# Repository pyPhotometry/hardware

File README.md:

# pyPhotometry Hardware

This repository contains design files for pyPhometry hardware.  For more information see: https://pyphotometry.readthedocs.io/en/latest/user-guide/hardware/

The repository contains the following devices:

## Acquisition board v1.0

The original version of the acquisition board as detailed in the [pyPhotometry manuscript](https://www.nature.com/articles/s41598-019-39724-y), featuring:

-  2 analog inputs (0-3.3V) for photoreceiver signals.
- 2 Digital inputs for registering behavioural events or sync pulses.
- 2 LED driver outputs with 0-100mA adjustable current output.

## Acquisition board v2.0

An updated version of the acquisition board with the following improvements from version 1.0:

- Increased maximum current of 300mA from the two LED driver outputs.
- 2 additional LED control outputs for triggering external LED drivers that require a voltage control signal (0-3.3V) , allowing the board to be used with optical hardware like the Doric Gen3 minicubes which have integrated LED drivers.  The signals output on the two LED control outputs are the same signals used to control the on-board LED drivers, so it is not possible to independently use the LED control outputs and the LED driver outputs at the same time.
- Reduced artefacts on analog input signals caused by saturation (i.e. voltage exceeding 3.3V) on the other analog input.
- Additional Picoblade connector providing access to 3 pyboard pins including I2C serial communication.  

## Acquisition board case

A plastic case compatible both v1.0 and v2.0 acquisition boards.

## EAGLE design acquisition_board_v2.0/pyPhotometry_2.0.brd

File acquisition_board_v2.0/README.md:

# Acquisition board v2.0

An updated version of the acquisition board with the following improvements from version 1.0:

- Increased maximum current of 300mA from the two LED driver outputs.
- 2 additional LED control outputs for triggering external LED drivers that require a voltage control signal (0-3.3V) , allowing the board to be used with optical hardware like the Doric Gen3 minicubes which have integrated LED drivers.  The signals output on the two LED control outputs are the same signals used to control the on-board LED drivers, so it is not possible to independently use the LED control outputs and the LED driver outputs at the same time.
- Reduced artefacts on analog input signals caused by saturation (i.e. voltage exceeding 3.3V) on the other analog input.
- Additional Picoblade connector providing access to 3 pyboard pins including I2C serial communication.

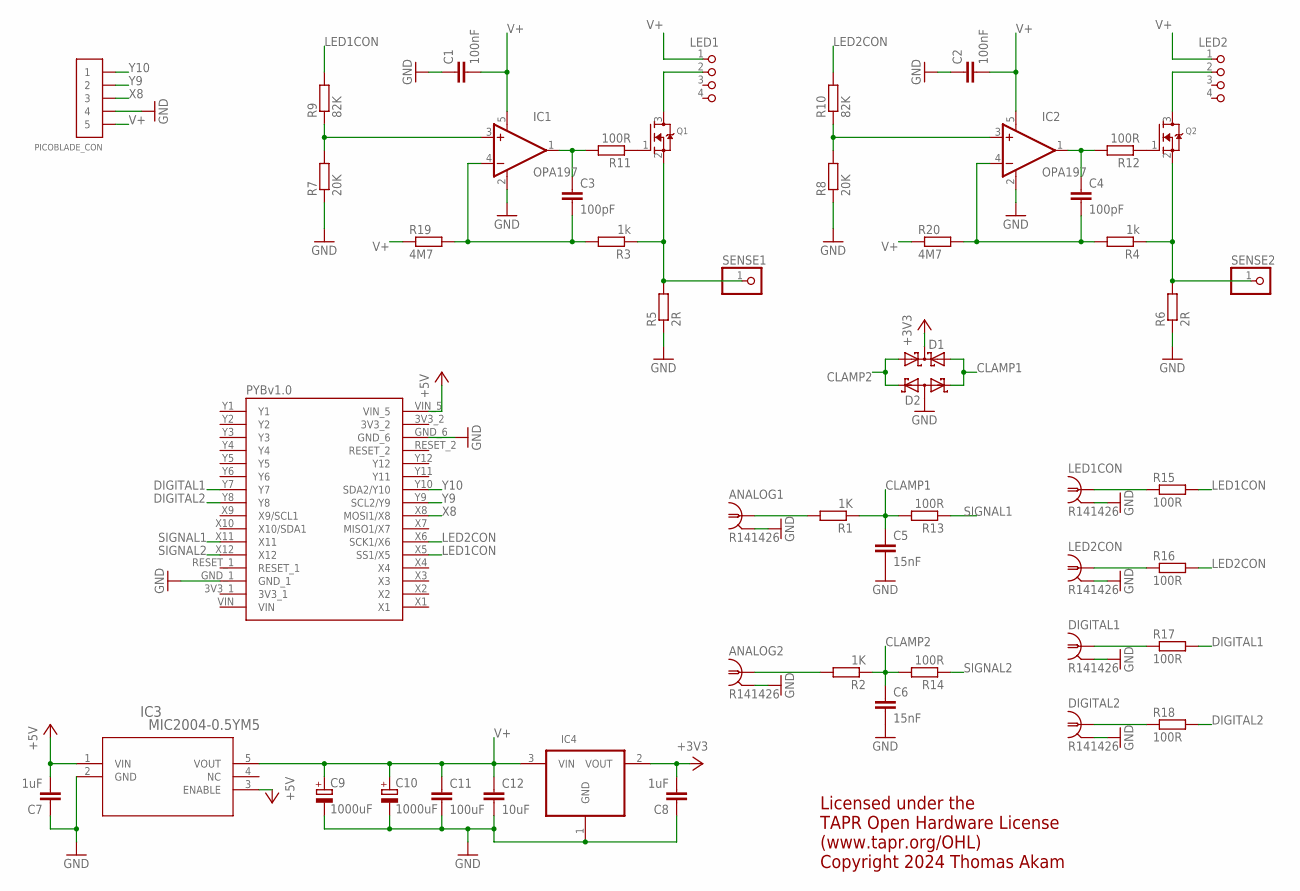
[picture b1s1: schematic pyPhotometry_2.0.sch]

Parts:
ANALOG1, ANALOG2: R141426
C1: 100nF; C0603K
C2: 100nF; C0603
C3, C4: 100pF; C0603K
C5, C6: 15nF; C0603K
C7, C8: 1uF; C0603
C9, C10: 1000uF; 153CLV-0807
C11: 100uF; C1206
C12: 10uF; C1206
D1: BAT54C; SOT23
D2: BAT54A; SOT23
DIGITAL1, DIGITAL2: R141426
IC1, IC2: OPA197; SOT23-5
IC3: MIC2004-0.5YM5; SOT-23-5_M5
IC4: MCP1700T-3302E/TT; SOT95P237X112-3N
LED1, LED2: M8-4
LED1CON, LED2CON: R141426
PICOBLADE_CON: CONN_5-1-53261; PB-53261-05
Q1, Q2: MOSFET-NREFLOW; SOT23
R1, R2: 1K; R0603
R3, R4: 1k; R0603
R5, R6: 2R; R0603
R7, R8: 20K; R0603
R9, R10: 82K; R0603
R11, R12, R13, R14, R15, R16, R17, R18: 100R; R0603
R19, R20: 4M7; R0603
SENSE1, SENSE2: PINHD-1X1; 1X01
U$1: PYBOARD-REDUCED-3

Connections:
+3V3: C8.2, D1.3 (CC), IC4.2 (VOUT)
+5V: C7.2, IC3.1 (VIN), IC3.3 (ENABLE), U$1.VIN_5
A1: ANALOG1.1, R1.2
A2: ANALOG2.1, R2.2
CLAMP1: C5.1, D1.2 (A2), D2.1 (K1), R1.1, R13.2
CLAMP2: C6.1, D1.1 (A1), D2.2 (K2), R2.1, R14.2
DIGITAL1: R17.2, U$1.Y7
DIGITAL2: R18.2, U$1.Y8
GND: ANALOG1.2 (GND), ANALOG1.3 (GND), ANALOG1.4 (GND), ANALOG1.5 (GND), ANALOG2.2 (GND), ANALOG2.3 (GND), ANALOG2.4 (GND), ANALOG2.5 (GND), C1.1, C2.1, C5.2, C6.2, C7.1, C8.1, C9.-, C10.-, C11.2, C12.2, D2.3 (AA), DIGITAL1.2 (GND), DIGITAL1.3 (GND), DIGITAL1.4 (GND), DIGITAL1.5 (GND), DIGITAL2.2 (GND), DIGITAL2.3 (GND), DIGITAL2.4 (GND), DIGITAL2.5 (GND), IC1.2 (V-), IC2.2 (V-), IC3.2 (GND), IC4.1 (GND), LED1CON.2 (GND), LED1CON.3 (GND), LED1CON.4 (GND), LED1CON.5 (GND), LED2CON.2 (GND), LED2CON.3 (GND), LED2CON.4 (GND), LED2CON.5 (GND), PICOBLADE_CON.4, R5.1, R6.1, R7.1, R8.1, U$1.GND_1, U$1.GND_6
LED1CON: R9.2, R15.2, U$1.X5 (SS1/X5)
LED2CON: R10.2, R16.2, U$1.X6 (SCK1/X6)
unnamed: C3.1, IC1.1 (OUT), R11.2
unnamed: C3.2, IC1.4 (-IN), R3.2, R19.2
unnamed: IC1.3 (+IN), R7.2, R9.1
unnamed: Q1.1 (G), R11.1
unnamed: LED1.2, Q1.3 (D)
unnamed: Q1.2 (S), R3.1, R5.2, SENSE1.1
unnamed: C4.1, IC2.1 (OUT), R12.2
unnamed: Q2.2 (S), R4.1, R6.2, SENSE2.1
unnamed: C4.2, IC2.4 (-IN), R4.2, R20.2
unnamed: IC2.3 (+IN), R8.2, R10.1
unnamed: Q2.1 (G), R12.1
unnamed: LED2.2, Q2.3 (D)
unnamed: DIGITAL1.1, R17.1
unnamed: LED1CON.1, R15.1
unnamed: DIGITAL2.1, R18.1
unnamed: LED2CON.1, R16.1
SIGNAL1: R13.1, U$1.X11
SIGNAL2: R14.1, U$1.X12
V+: C1.2, C2.2, C9.+, C10.+, C11.1, C12.1, IC1.5 (V+), IC2.5 (V+), IC3.5 (VOUT), IC4.3 (VIN), LED1.1, LED2.1, PICOBLADE_CON.5, R19.1, R20.1
X8: PICOBLADE_CON.3, U$1.X8 (MOSI1/X8)
Y9: PICOBLADE_CON.2, U$1.Y9 (SCL2/Y9)
Y10: PICOBLADE_CON.1, U$1.Y10 (SDA2/Y10)

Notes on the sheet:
Licensed under the TAPR Open Hardware License (www.tapr.org/OHL) Copyright 2024 Thomas Akam

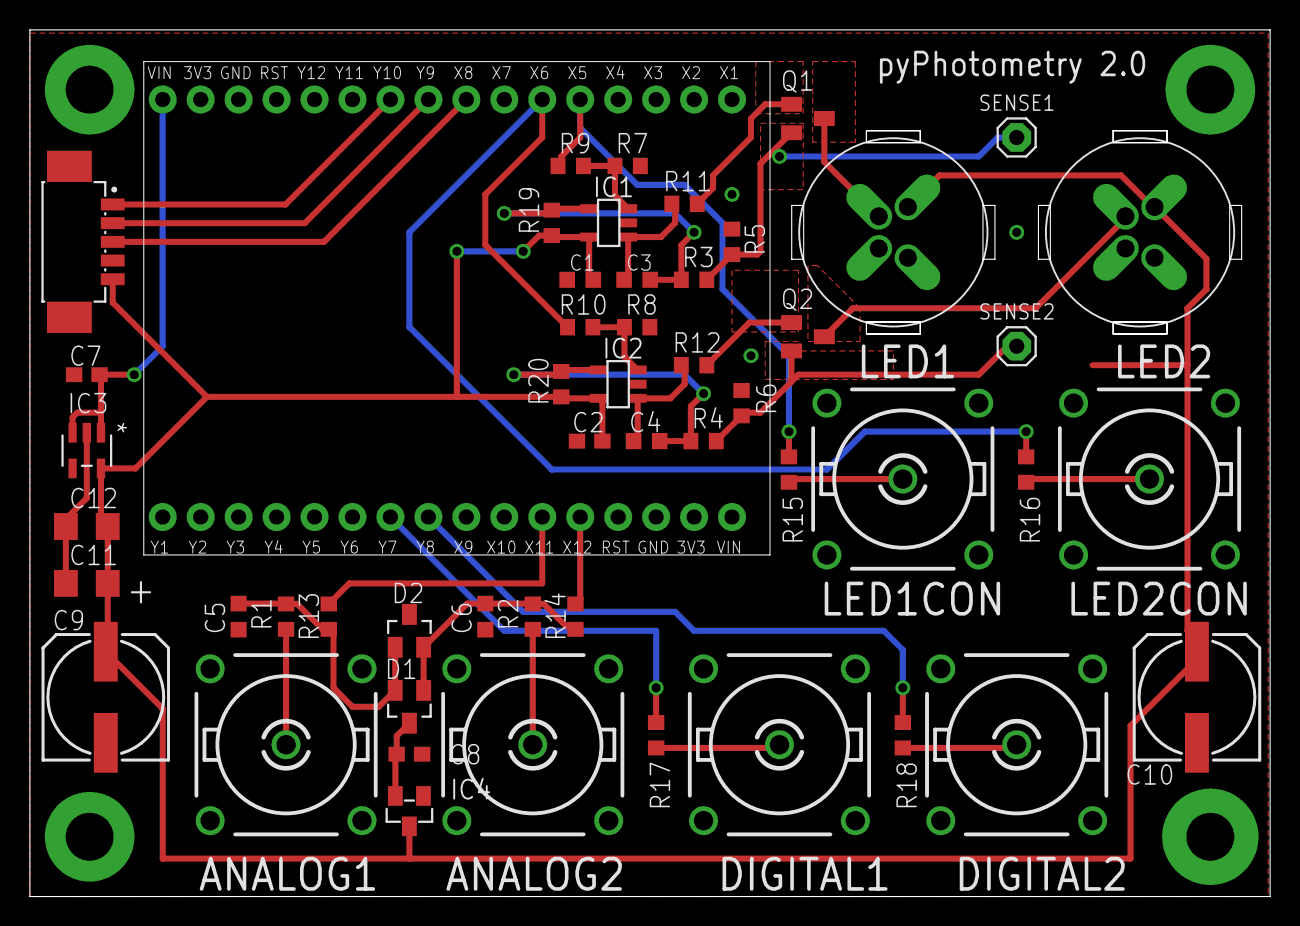
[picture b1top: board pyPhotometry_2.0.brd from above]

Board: 2 copper layers, 83.0 x 58.0 mm, 52 parts (0 on the bottom side), 33 nets.

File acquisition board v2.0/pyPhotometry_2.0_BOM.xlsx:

Part | Value | Device | Package | Description | MF | MPN | OC_FARNELL
SIGNAL1 |  | - | - | BNC connector | TE CONNECTIVITY | 1-1337445-0 | 1205964
SIGNAL2 |  | - | - | BNC connector | TE CONNECTIVITY | 1-1337445-0 | 1205964
DIGITAL1 |  | - | - | BNC connector | TE CONNECTIVITY | 1-1337445-0 | 1205964
DIGITAL2 |  | - | - | BNC connector | TE CONNECTIVITY | 1-1337445-0 | 1205964
LED1CON |  | - | - | BNC connector | TE CONNECTIVITY | 1-1337445-0 | 1205964
LED2CON |  | - | - | BNC connector | TE CONNECTIVITY | 1-1337445-0 | 1205964
LED1 | - | - | - | M8 connector | TE CONNECTIVITY | T4041037041-000 | 2817801
LED2 | - | - | - | M8 connector | TE CONNECTIVITY | T4041037041-000 | 2817801
PICOBLADE_CON | - | - | - | Picoblade connector | Molex | 53261-0571 | 1125360
IC1 | - | OPA197 | SOT23-5 | Op amp | Texas Instruments | OPA197IDBVT | 2545356
IC2 | - | OPA197 | SOT23-5 | Op amp | Texas Instruments | OPA197IDBVT | 2545356
IC3 | - | MIC2004-0.5YM5 | SOT23-5 | Current limiting switch | Microchip | MIC2004-0.5YM5-TR | 2509877
IC4 |  | MCP1700T-3302E/TT | SOT23-3 | Voltage regulator | Microchip | MCP1700T-3302E/TT | 1296592
C1 | 100nF | - | 0603 | Capacitor | Generic | GPC0603104
C2 | 100nF | - | 0603 | Capacitor | Generic | GPC0603104
C3 | 100pF | - | 0603 | Capacitor | Generic | GPC0603101
C4 | 100pF | - | 0603 | Capacitor | Generic | GPC0603101
C5 | 15nF | - | 0603 | Capacitor | Generic | GPC0603153
C6 | 15nF | - | 0603 | Capacitor | Generic | GPC0603153
C7 | 1uF | - | 0603 | Capacitor | Generic | GPC0603105
C8 | 1uF | - | 0603 | Capacitor | Generic | GPC0603105
C9 | 1000uF | - | - | Capacitor | MULTICOMP | MCVVT6R3M102FB3 | 2611416
C10 | 1000uF | - | - | Capacitor | MULTICOMP | MCVVT6R3M102FB3 | 2611416
C11 | 100uF | - | 1206 | Capacitor | KEMET | T490A107M006ATE500 | 2688577
C12 | 10uF | - | 1206 | Capacitor | Generic | GPC1206106
D1 | - | - | - | Schottky Diode | STMICROELECTRONICS | BAR43CFILM | 9801383
D2 | - | - | - | Schottky Diode | STMICROELECTRONICS | BAR43AFILM | 1611382
Q1 | - | - | SOT23 | Mosfet | Diodes Inc | DMG2302UK-7 | 3127315
Q2 | - | - | SOT23 | Mosfet | Diodes Inc | DMG2302UK-7 | 3127315
R1 | 1K | - | 0603 | Resistor | Generic | GPR06031K
R2 | 1K | - | 0603 | Resistor | Generic | GPR06031K
R3 | 1K | - | 0603 | Resistor | Generic | GPR06031K
R4 | 1K | - | 0603 | Resistor | Generic | GPR06031K
R5 | 2R | - | 0603 | Resistor | Generic | GPR06032R
R6 | 2R | - | 0603 | Resistor | Generic | GPR06032R
R7 | 20K | - | 0603 | Resistor | Generic | GPR060320K
R8 | 20K | - | 0603 | Resistor | Generic | GPR060320K
R9 | 82K | - | 0603 | Resistor | Generic | GPR060382K
R10 | 82K | - | 0603 | Resistor | Generic | GPR060382K
R11 | 100R | - | 0603 | Resistor | Generic | GPR0603100R
R12 | 100R | - | 0603 | Resistor | Generic | GPR0603100R
R13 | 100R | - | 0603 | Resistor | Generic | GPR0603100R
R14 | 100R | - | 0603 | Resistor | Generic | GPR0603100R
R15 | 100R | - | 0603 | Resistor | Generic | GPR0603100R
R16 | 100R | - | 0603 | Resistor | Generic | GPR0603100R
R17 | 100R | - | 0603 | Resistor | Generic | GPR0603100R
R18 | 100R | - | 0603 | Resistor | Generic | GPR0603100R
R19 | 4M7 | - | 0603 | Resistor | Generic | GPR06034M7
R20 | 4M7 | - | 0603 | Resistor | Generic | GPR06034M7
PYBOARD_CON_1 |  | - | - | 1x16 receptacle | SAMTEC | CES-116-01-T-S | 1667522
PYBOARD_CON_2 |  | - | - | 1x16 receptacle | SAMTEC | CES-116-01-T-S | 1667522
PYBOARD_CON_3 |  | - | - | 1x16 header | SAMTEC | TSW-116-06-T-S | 2035403
PYBOARD_CON_4 |  | - | - | 1x16 header | SAMTEC | TSW-116-06-T-S | 2035403
PYBOARD |  | PYBOARD v1.1 | - | PYBOARD v1.1 | https://micropython.org/store | PYBv1.1 | -
Licensed under the TAPR Open Hardware License (www.tapr.org/OHL)
Copyright 2024 Thomas Akam

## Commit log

2018-10-02 Initial commit.
2018-10-03 - Moved acquisition board files to seperate folder.
    - Added optics_BOM
2018-10-08 - Increaced slot width for M8 connectors for compatibility with OEPS PCB fabrication.
    - Added PDF of board.
2018-10-17 - Fixed incorrect NA on rotary-sample fiber in optics BOM.
2018-11-06 - Fixed part number for minicube clamp in optic BOM.
2018-11-29 - Optics_BOM: Changed fiber connecting LEDs to minicube from 0.22 to 0.48NA.
2021-03-23 prepare board for kitspace
2021-03-23 add kitspace.yaml file
2021-03-27 regenerate gerber files as jlcpcb had an issue with the original ones
2021-04-16 add small description of kitspace to readem
2024-08-21 Added version number to acqusition board folder name.
2025-01-17 Added acqusition board v2.0 and acquisition board case.
2025-01-17 Replaced spaces with underscores in folder names
2025-01-17 Added pdf of v2.0 board schematic.
2025-01-23 Edited readmes for v2.0 board.
2025-01-30 Added gerber files for the acqusition boards
2025-10-21 Added threaded mounting holes to bottom of case.
2025-11-25 Added version of case for use with OEPS pyboard.
